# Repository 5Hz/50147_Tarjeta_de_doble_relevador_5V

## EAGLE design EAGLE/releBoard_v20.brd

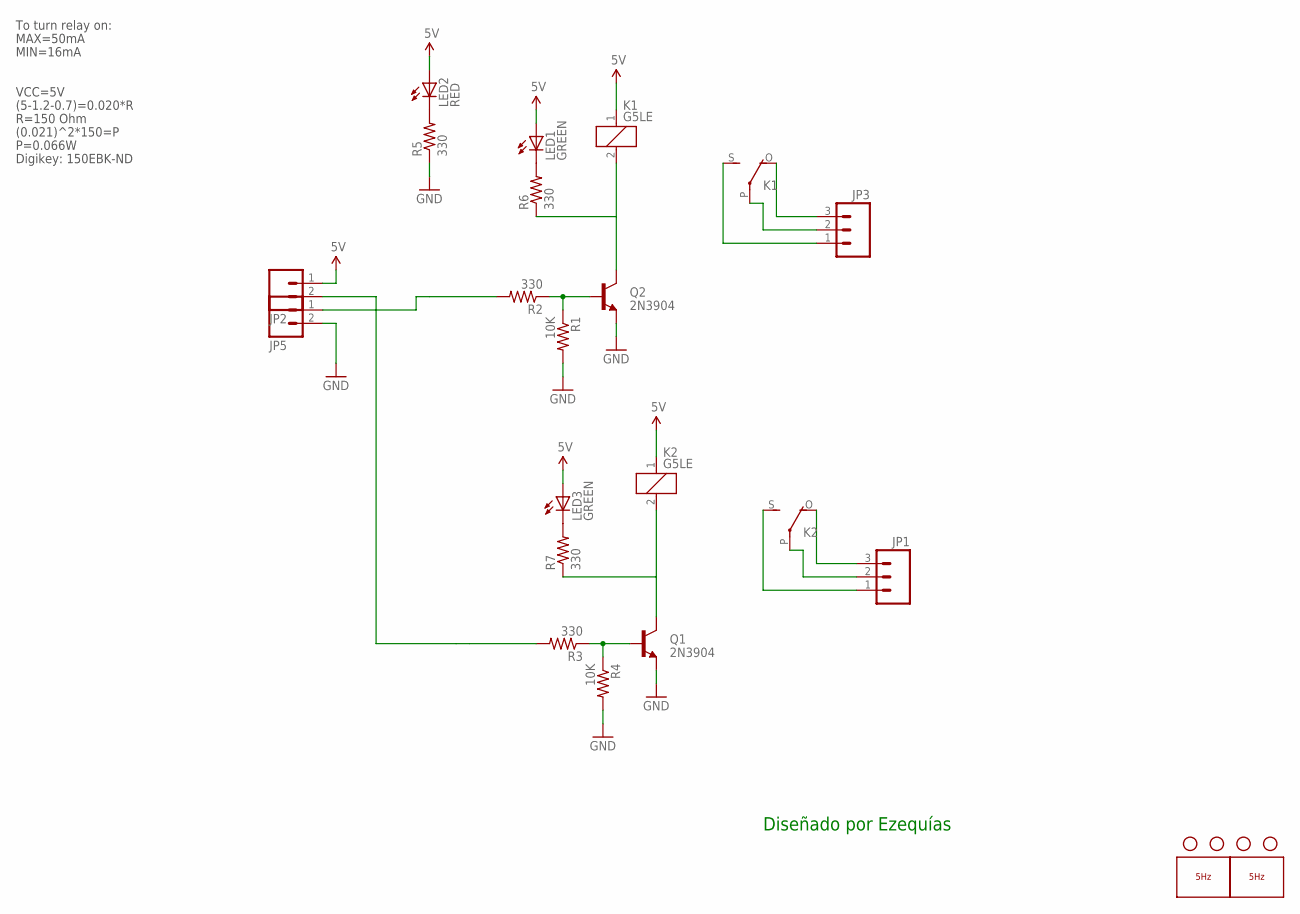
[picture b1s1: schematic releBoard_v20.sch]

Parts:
JP1, JP3: M03-SCREW-5MM; SCREWTERMINAL-5MM-3
JP2, JP5: M025MM; SCREWTERMINAL-5MM-2
K1, K2: G5LE
LED1, LED3: GREEN; LED-0603
LED2: RED; LED-0603
LOGO1: LOGO_5HZ_H_15MM; 5HZ_LOGO_H_15MM
LOGO2: LOGO_5HZ_WEB_COOPER_10MM; 5HZ_WEB_COOPER_10MM
Q1, Q2: 2N3904; SOT23
R1, R4: 10K; 0603-RES
R2, R3, R5, R6, R7: 330; 0603-RES
U$3, U$4, U$5, U$7: STAND-OFF

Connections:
5V: JP2.1, K1.1, K2.1, LED1.A, LED2.A, LED3.A
COIL: K1.2, Q2.3 (C), R6.1
COIL1: K2.2, Q1.3 (C), R7.1
GND: JP5.2, Q1.2 (E), Q2.2 (E), R1.2, R4.2, R5.1
LINE: JP3.2, K1.P
LINE1: JP1.2, K2.P
unnamed: JP5.1, R2.2
unnamed: Q1.1 (B), R3.1, R4.1
unnamed: LED1.C, R6.2
unnamed: LED2.C, R5.2
unnamed: JP2.2, R3.2
unnamed: Q2.1 (B), R1.1, R2.1
unnamed: LED3.C, R7.2
NC: JP3.3, K1.O
NC1: JP1.3, K2.O
NO: JP3.1, K1.S
NO1: JP1.1, K2.S

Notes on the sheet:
To turn relay on:
(5-1.2-0.7)=0.020*R
R=150 Ohm
VCC=5V
MAX=50mA
MIN=16mA
(0.021)^2*150=P
P=0.066W
Digikey: 150EBK-ND
Diseñado por Ezequías

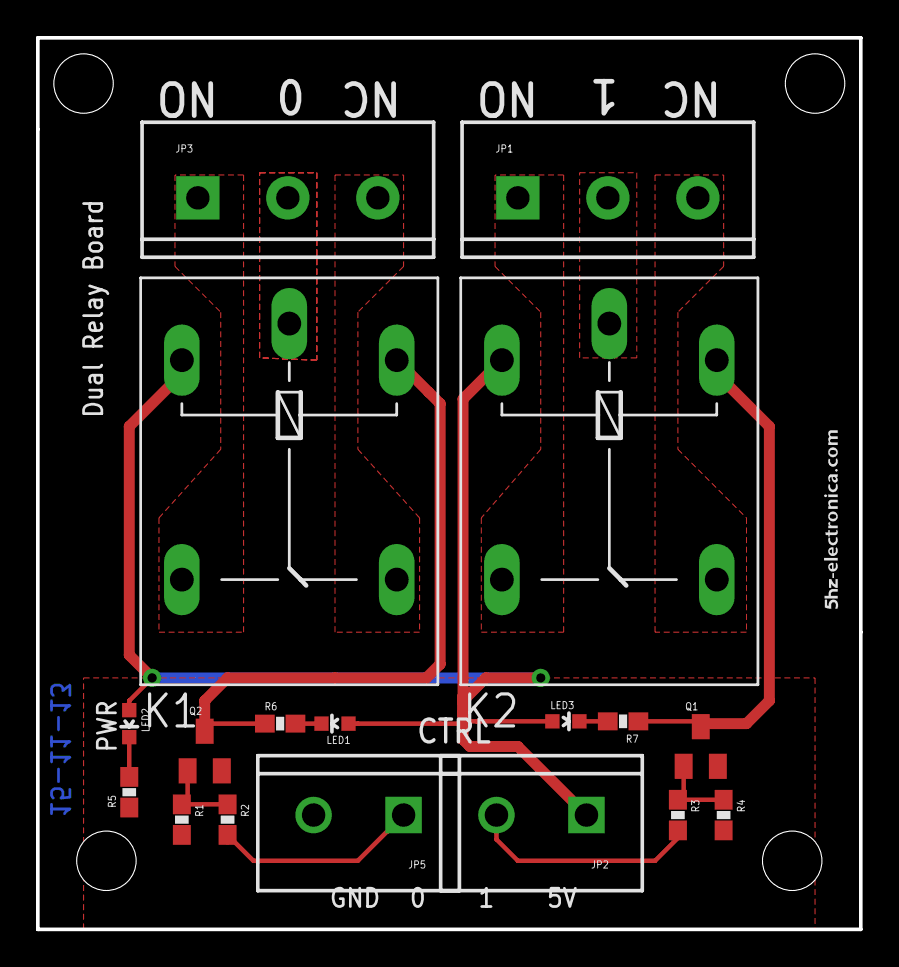
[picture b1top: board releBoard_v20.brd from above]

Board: 2 copper layers, 45.7 x 49.5 mm, 24 parts (1 on the bottom side), 17 nets.

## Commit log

2014-03-31 Creación

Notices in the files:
parts and their libraries:
SparkFun_old: Licensing: CC v3.0 Share-Alike You are welcome to use this library for commercial purposes.
